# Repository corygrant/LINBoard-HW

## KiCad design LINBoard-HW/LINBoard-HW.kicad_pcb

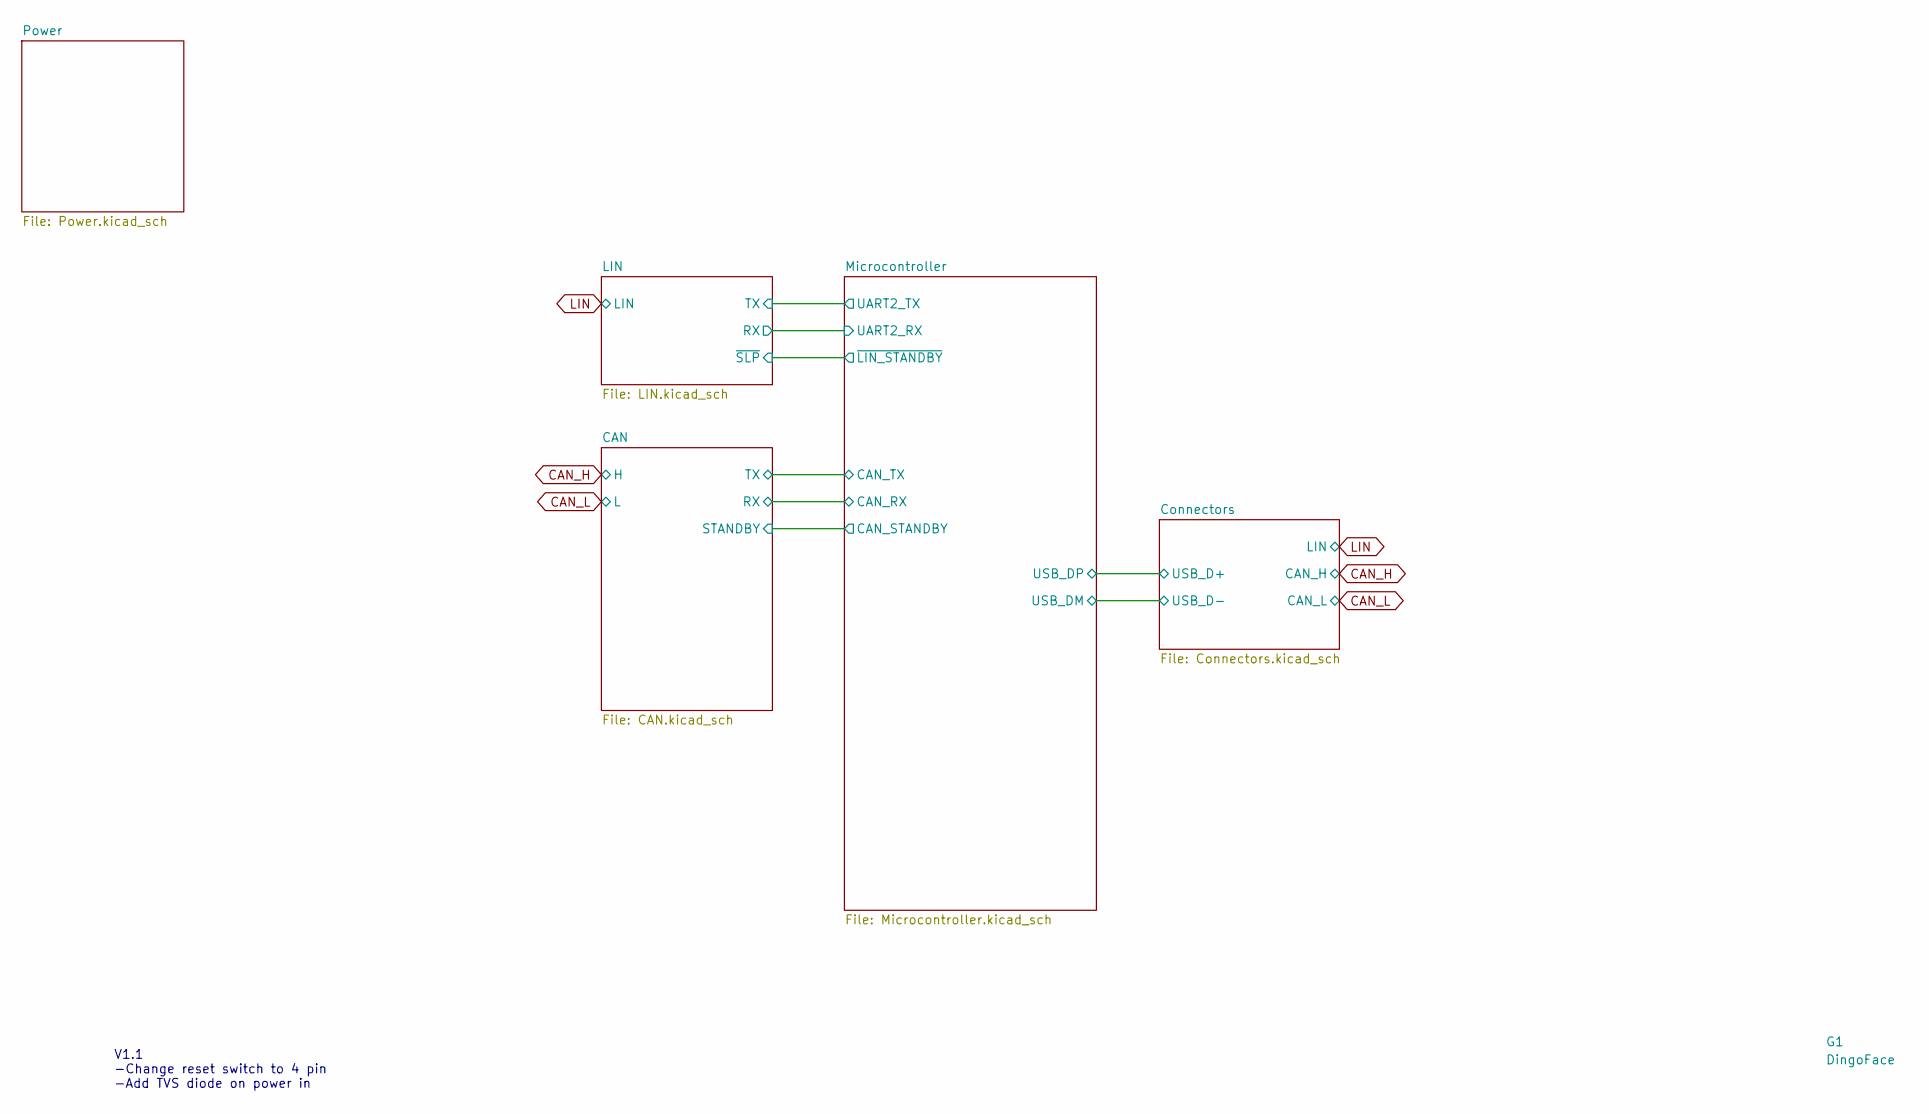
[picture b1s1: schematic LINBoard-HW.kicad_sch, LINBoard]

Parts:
G1: DingoFace; DingoFaceNoFill

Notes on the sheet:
V1.1 -Change reset switch to 4 pin -Add TVS diode on power in

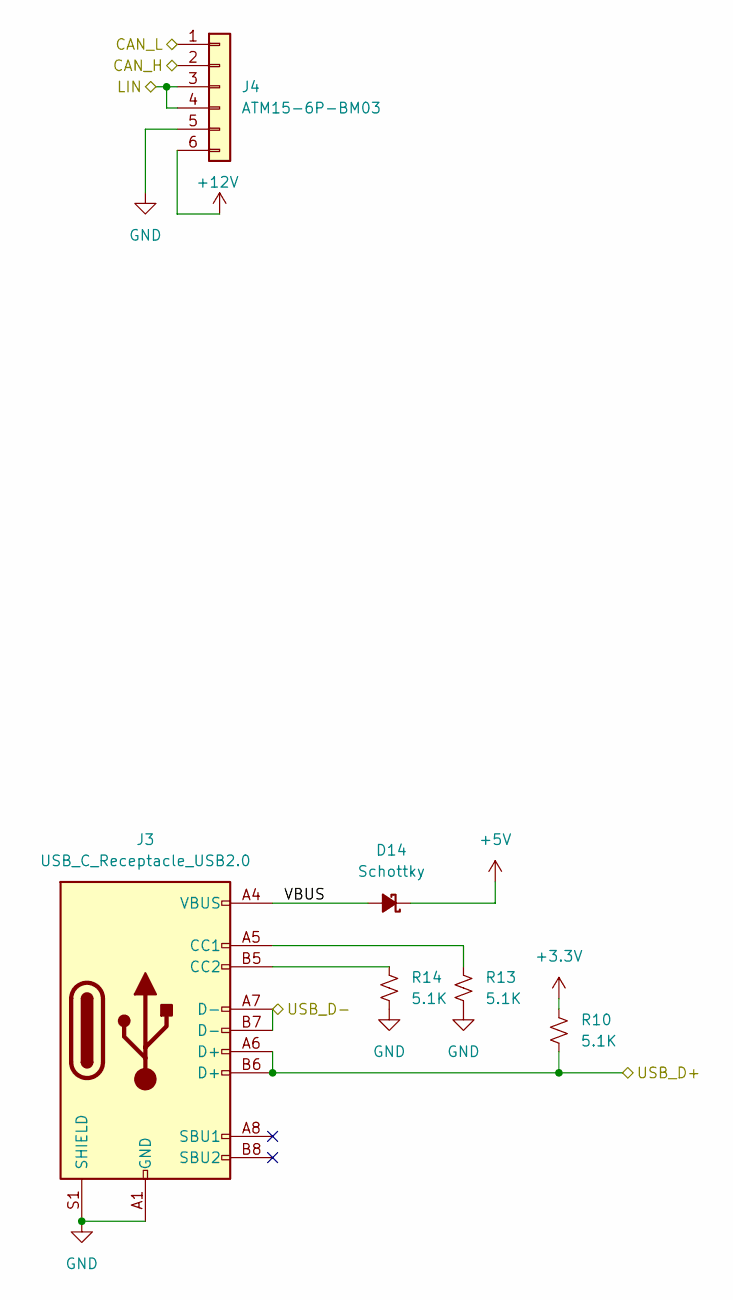
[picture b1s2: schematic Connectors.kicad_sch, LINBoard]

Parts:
D14: Schottky; D_SOD-123; LCSC Part C179426
J3: USB_C_Receptacle_USB2.0; USB_C_Receptacle_GCT_USB4085; Digi-Key_PN 2073-USB4085-GF-ACT-ND
J4: ATM15-6P-BM03; ATM13-6P
R10, R13, R14: 5.1K; R_0805_2012Metric; LCSC Part C27834

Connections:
+3.3V: R10.1; also elsewhere on the board
+5V: D14.1 (K); also elsewhere on the board
+12V: J4.6; also elsewhere on the board
/Connectors/USB_D+: J3.A6 (D+), J3.B6 (D+), R10.2; also elsewhere on the board
/Connectors/USB_D-: J3.A7 (D-), J3.B7 (D-); also elsewhere on the board
/Connectors/VBUS: D14.2 (A), J3.A4 (VBUS), J3.A9 (VBUS), J3.B4 (VBUS), J3.B9 (VBUS)
CAN_H: J4.2; also elsewhere on the board
CAN_L: J4.1; also elsewhere on the board
GND: J3.A1 (GND), J3.A12 (GND), J3.B1 (GND), J3.B12 (GND), J3.S1 (SHIELD), J4.5, R13.2, R14.2; also elsewhere on the board
LIN: J4.3, J4.4; also elsewhere on the board
unnamed: J3.A5 (CC1), R13.1
unnamed: J3.B5 (CC2), R14.1

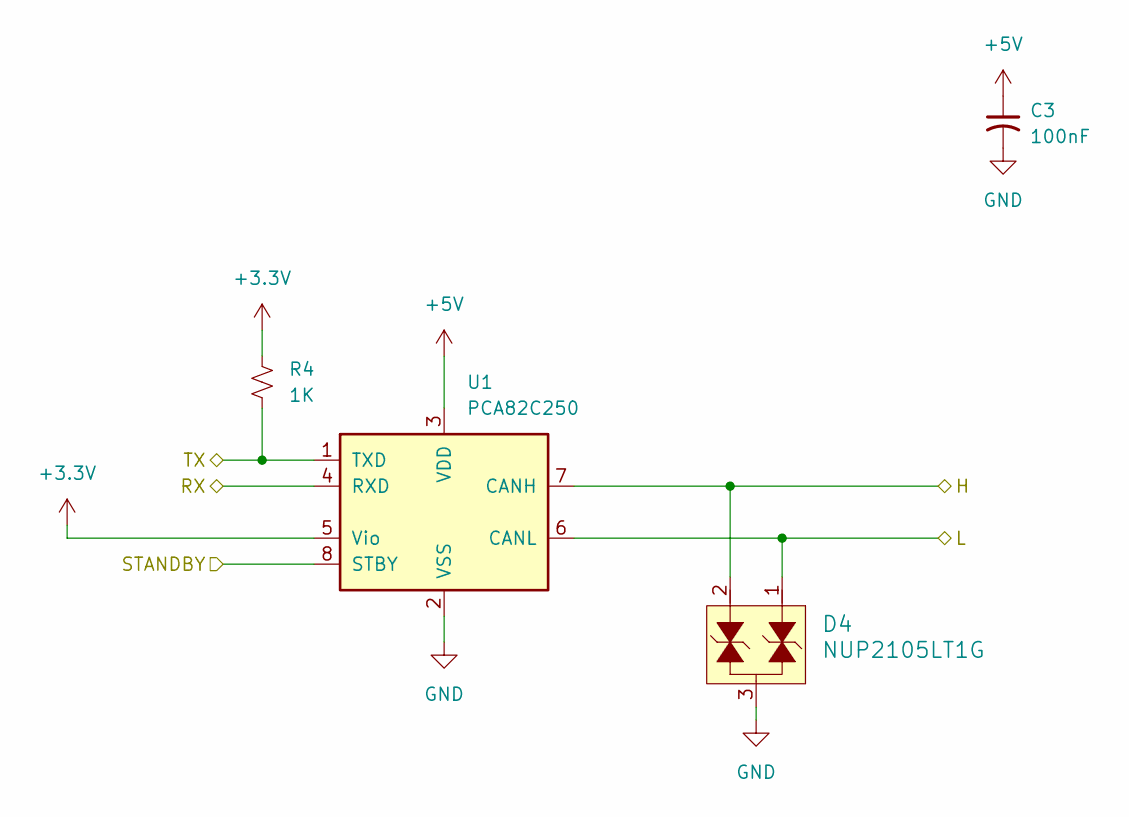
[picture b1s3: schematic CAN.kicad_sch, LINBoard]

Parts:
C3: 100nF; C_0805_2012Metric; LCSC Part C49678
D4: NUP2105LT1G; SOT-23-3; MPN NUP2105LT1G; Digi-Key_PN NUP2105LT1GOSCT-ND
R4: 1K; R_0805_2012Metric; LCSC Part C17513
U1: PCA82C250; SOIC-8_3.9x4.9mm_P1.27mm; LCSC Part C7439

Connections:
+3.3V: R4.1, U1.5 (Vio); also elsewhere on the board
+5V: C3.1, U1.3 (VDD); also elsewhere on the board
/CAN/RX: U1.4 (RXD); also elsewhere on the board
/CAN/STANDBY: U1.8 (STBY); also elsewhere on the board
/CAN/TX: R4.2, U1.1 (TXD); also elsewhere on the board
CAN_H: D4.2, U1.7 (CANH); also elsewhere on the board
CAN_L: D4.1, U1.6 (CANL); also elsewhere on the board
GND: C3.2, D4.3, U1.2 (VSS); also elsewhere on the board

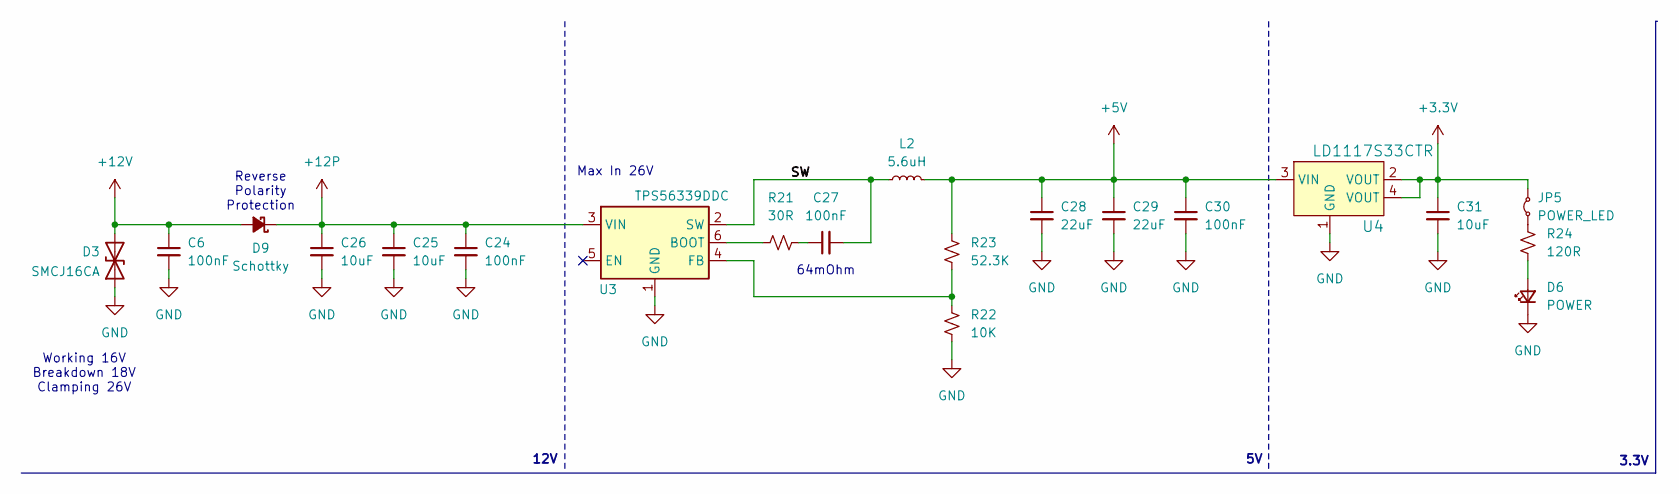
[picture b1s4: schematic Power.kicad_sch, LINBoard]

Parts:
C6: 100nF; C_0805_2012Metric; LCSC Part C15850
C24, C27, C30: 100nF; C_0805_2012Metric; LCSC Part C49678
C25, C26, C31: 10uF; C_0805_2012Metric; LCSC Part C15850
C28, C29: 22uF; C_0805_2012Metric; LCSC Part C45783
D3: SMCJ16CA; DO-214AB_TVS
D6: POWER; LED_0805_2012Metric; LCSC Part C2297
D9: Schottky; D_SOD-123; LCSC Part C179426
JP5: POWER_LED; SolderJumper-2_P1.3mm_Bridged_RoundedPad1.0x1.5mm
L2: 5.6uH; Wuerth_LHMI; LCSC Part C467062
R21: 30R; R_0805_2012Metric; LCSC Part C325808
R22: 10K; R_0805_2012Metric; LCSC Part C17414
R23: 52.3K; R_0805_2012Metric; LCSC Part C17740
R24: 120R; R_0805_2012Metric; LCSC Part C17437
U3: TPS56339DDC; SOT-23-6; LCSC Part C2071106
U4: LD1117S33CTR; SOT-223; MPN LD1117S33CTR; Digi-Key_PN 497-1241-1-ND

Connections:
+3.3V: C31.1, JP5.2 (B), U4.2 (VOUT), U4.4 (VOUT); also elsewhere on the board
+5V: C28.1, C29.1, C30.1, L2.2, R23.2, U4.3 (VIN); also elsewhere on the board
+12P: C24.1, C25.1, C26.1, D9.1 (K), U3.3 (VIN); also elsewhere on the board
+12V: C6.1, D3.2 (A2), D9.2 (A); also elsewhere on the board
/Power/SW: C27.2, L2.1, U3.2 (SW)
GND: C6.2, C24.2, C25.2, C26.2, C28.2, C29.2, C30.2, C31.2, D3.1 (A1), D6.1 (K), R22.1, U3.1 (GND), U4.1 (GND); also elsewhere on the board
unnamed: C27.1, R21.2
unnamed: D6.2 (A), R24.2
unnamed: JP5.1 (A), R24.1
unnamed: R21.1, U3.6 (BOOT)
unnamed: R22.2, R23.1, U3.4 (FB)

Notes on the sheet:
Working 16V Breakdown 18V Clamping 26V
64mOhm
Reverse Polarity Protection
12V
3.3V
Max In 26V

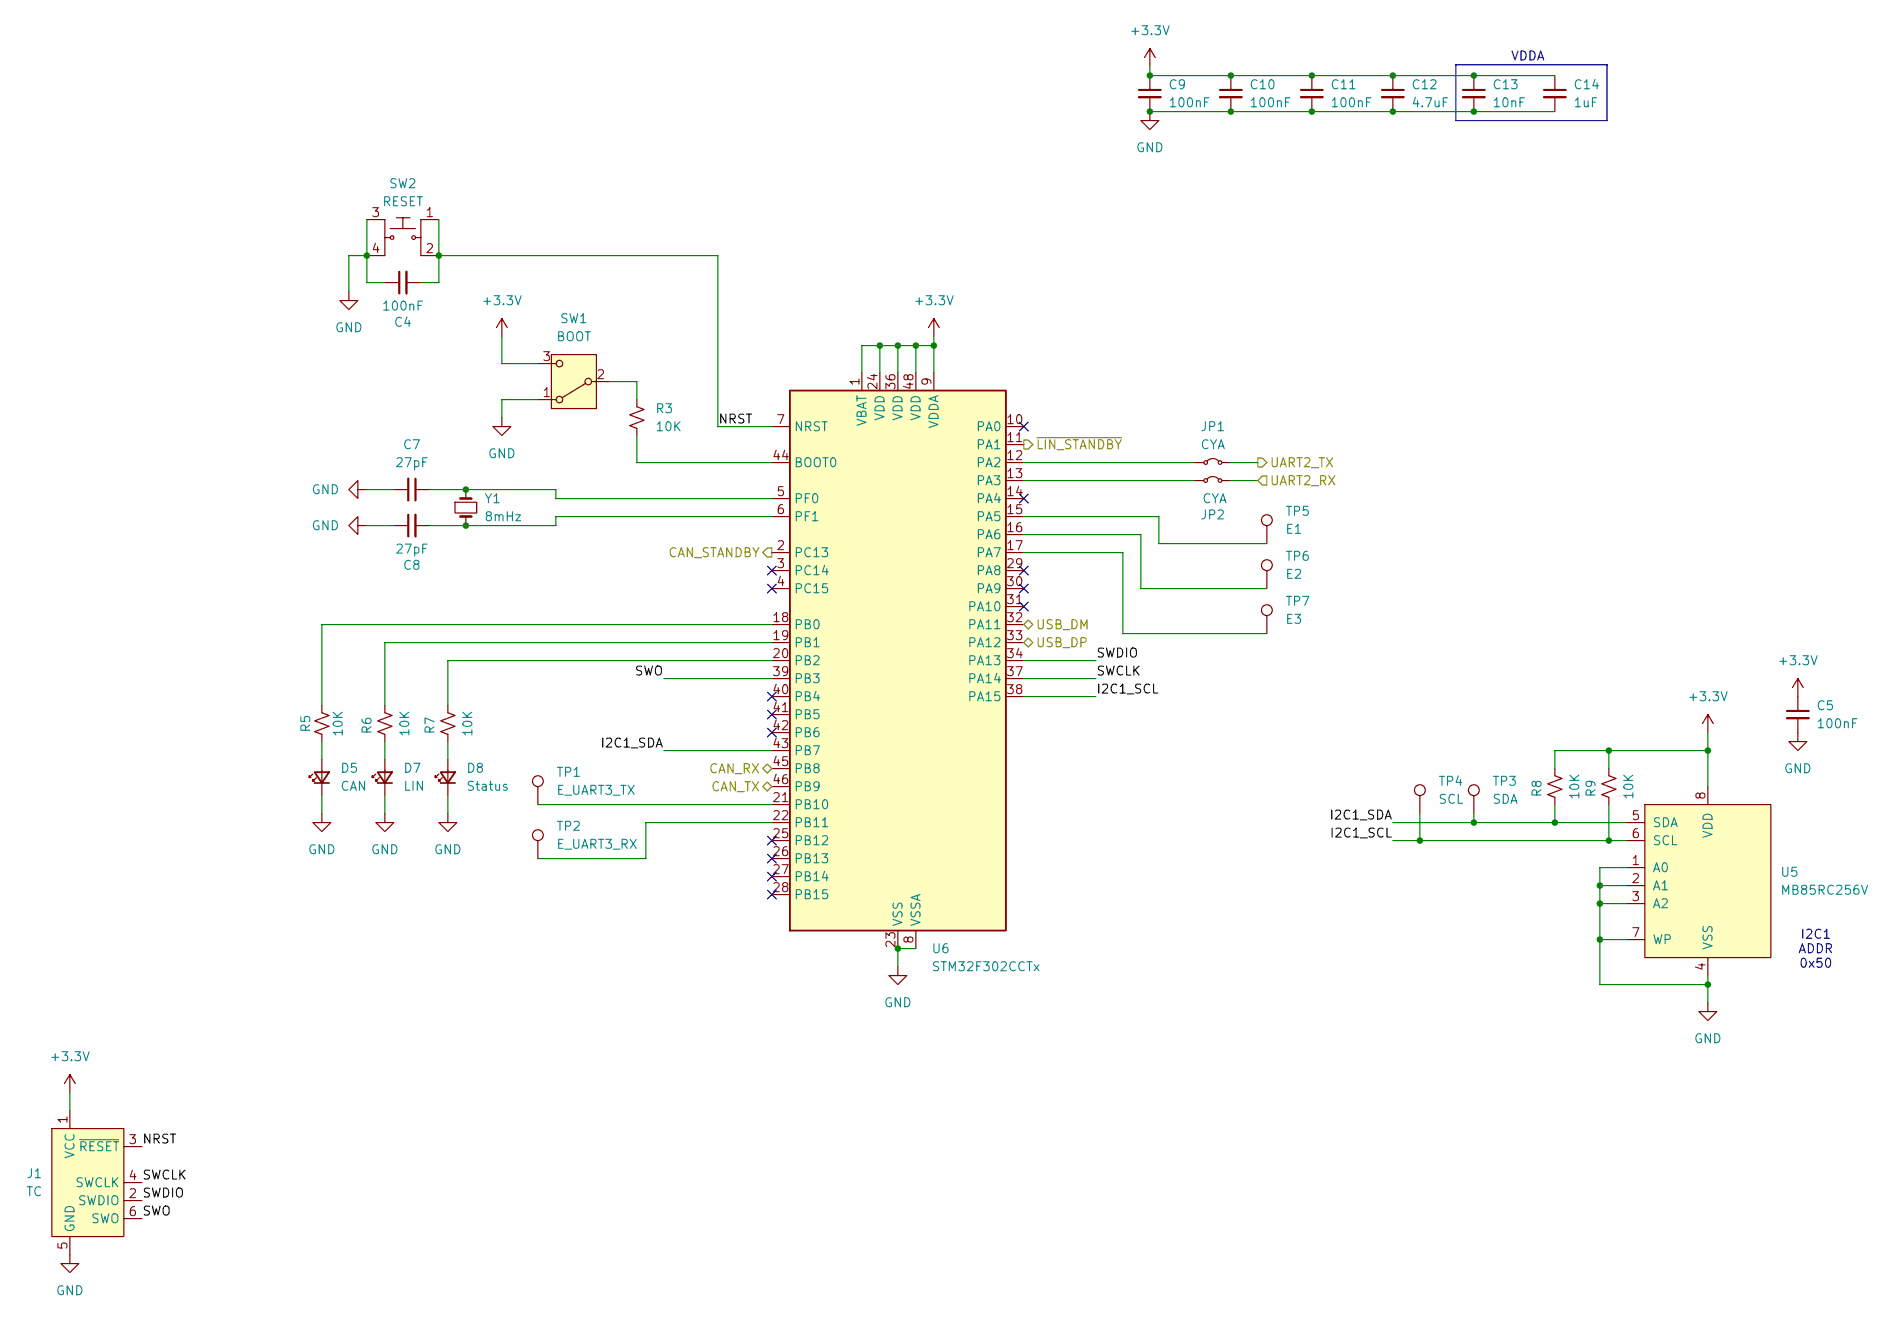
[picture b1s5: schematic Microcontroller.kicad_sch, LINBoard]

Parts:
C4, C5, C9, C10, C11: 100nF; C_0805_2012Metric; LCSC Part C49678
C7, C8: 27pF; C_0805_2012Metric; LCSC Part C1808
C12: 4.7uF; C_0805_2012Metric; LCSC Part C1779
C13: 10nF; C_0805_2012Metric; LCSC Part C1710
C14: 1uF; C_0805_2012Metric; LCSC Part C28323
D5: CAN; LED_0805_2012Metric; LCSC Part C2296
D7: LIN; LED_0805_2012Metric; LCSC Part C2296
D8: Status; LED_0805_2012Metric; LCSC Part C2297
J1: TC; Tag-Connect_TC2030-IDC-NL_2x03_P1.27mm_Vertical
JP1, JP2: CYA; SolderJumper-2_P1.3mm_Bridged2Bar_RoundedPad1.0x1.5mm
R3, R5, R6, R7, R8, R9: 10K; R_0805_2012Metric; LCSC Part C17414
SW1: BOOT; CJS-1200TB
SW2: RESET; SW-SMD_4P-L5.1-W5.1-P3.70-LS6.5-TL_H1.5; LCSC Part C318884
TP1: E_UART3_TX; TestPoint_Keystone_5000-5004_Miniature
TP2: E_UART3_RX; TestPoint_Keystone_5000-5004_Miniature
TP3: SDA; TestPoint_Keystone_5000-5004_Miniature
TP4: SCL; TestPoint_Keystone_5000-5004_Miniature
TP5: E1; TestPoint_Keystone_5000-5004_Miniature
TP6: E2; TestPoint_Keystone_5000-5004_Miniature
TP7: E3; TestPoint_Keystone_5000-5004_Miniature
U5: MB85RC256V; SOIC-8_3.9x4.9mm_P1.27mm; LCSC Part C47538
U6: STM32F302CCTx; LQFP-48_7x7mm_P0.5mm; LCSC Part C262946
Y1: 8mHz; Crystal_SMD_5032-2Pin_5.0x3.2mm_HandSoldering; LCSC Part C144380

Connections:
+3.3V: C5.1, C9.1, C10.1, C11.1, C12.1, C13.1, C14.1, J1.1 (VCC), R8.1, R9.1, SW1.3 (C), U5.8 (VDD), U6.1 (VBAT), U6.9 (VDDA), U6.24 (VDD), U6.36 (VDD), U6.48 (VDD); also elsewhere on the board
/CAN/RX: U6.45 (PB8); also elsewhere on the board
/CAN/STANDBY: U6.2 (PC13); also elsewhere on the board
/CAN/TX: U6.46 (PB9); also elsewhere on the board
/Connectors/USB_D+: U6.33 (PA12); also elsewhere on the board
/Connectors/USB_D-: U6.32 (PA11); also elsewhere on the board
/LIN/RX: JP2.2 (B); also elsewhere on the board
/LIN/TX: JP1.2 (B); also elsewhere on the board
/LIN/~SLP: U6.11 (PA1); also elsewhere on the board
/Microcontroller/I2C1_SCL: R9.2, TP4.1, U5.6 (SCL), U6.38 (PA15)
/Microcontroller/I2C1_SDA: R8.2, TP3.1, U5.5 (SDA), U6.43 (PB7)
/Microcontroller/NRST: C4.2, J1.3 (~RESET), SW2.1, SW2.2, U6.7 (NRST)
/Microcontroller/SWCLK: J1.4 (SWCLK), U6.37 (PA14)
/Microcontroller/SWDIO: J1.2 (SWDIO), U6.34 (PA13)
/Microcontroller/SWO: J1.6 (SWO), U6.39 (PB3)
GND: C4.1, C5.2, C7.2, C8.1, C9.2, C10.2, C11.2, C12.2, C13.2, C14.2, D5.1 (K), D7.1 (K), D8.1 (K), J1.5 (GND), SW1.1 (A), SW2.3, SW2.4, U5.1 (A0), U5.2 (A1), U5.3 (A2), U5.4 (VSS), U5.7 (WP), U6.8 (VSSA), U6.23 (VSS), U6.35 (VSS), U6.47 (VSS); also elsewhere on the board
unnamed: D5.2 (A), R5.2
unnamed: D7.2 (A), R6.2
unnamed: D8.2 (A), R7.2
unnamed: JP1.1 (A), U6.12 (PA2)
unnamed: JP2.1 (A), U6.13 (PA3)
unnamed: R3.2, SW1.2 (B)
unnamed: R3.1, U6.44 (BOOT0)
unnamed: TP5.1, U6.15 (PA5)
unnamed: TP6.1, U6.16 (PA6)
unnamed: TP7.1, U6.17 (PA7)
unnamed: R5.1, U6.18 (PB0)
unnamed: R6.1, U6.19 (PB1)
unnamed: R7.1, U6.20 (PB2)
unnamed: TP1.1, U6.21 (PB10)
unnamed: TP2.1, U6.22 (PB11)
unnamed: C7.1, U6.5 (PF0), Y1.1
unnamed: C8.2, U6.6 (PF1), Y1.2

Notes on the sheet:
VDDA
I2C1 ADDR 0x50

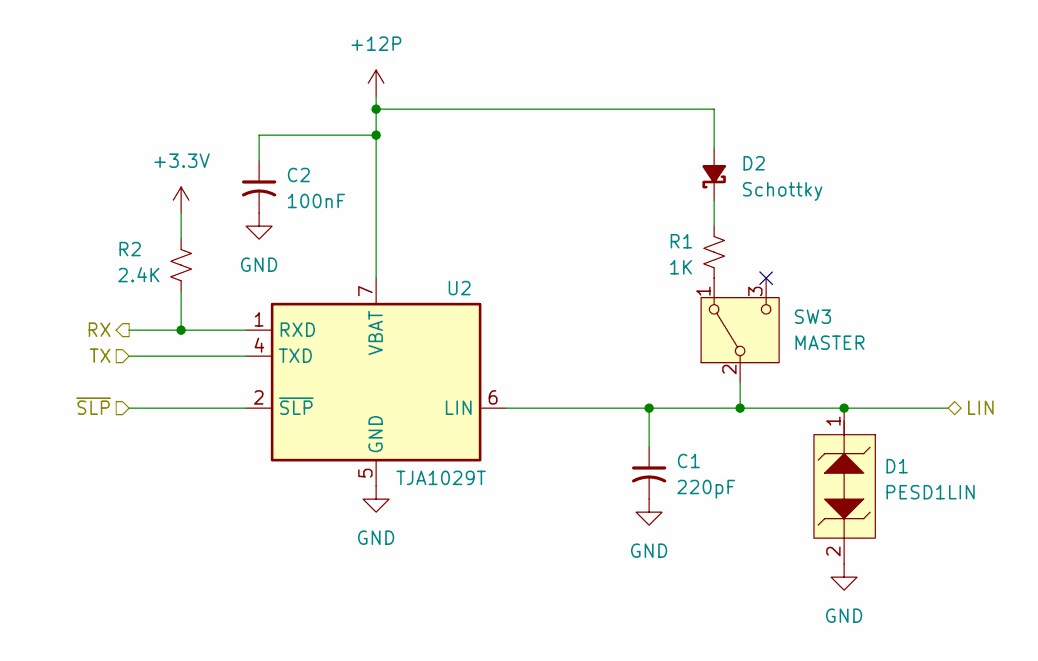
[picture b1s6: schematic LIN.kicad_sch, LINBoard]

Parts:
C1: 220pF; C_0805_2012Metric; LCSC Part C576920
C2: 100nF; C_0805_2012Metric; LCSC Part C49678
D1: PESD1LIN; D_SOD-323; LCSC Part C2858716
D2: Schottky; D_SOD-123; LCSC Part C179426
R1: 1K; R_0805_2012Metric; LCSC Part C17513
R2: 2.4K; R_0805_2012Metric; LCSC Part C17526
SW3: MASTER; CJS-1200TB
U2: TJA1029T; SOIC-8_3.9x4.9mm_P1.27mm; LCSC Part C194435

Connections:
+3.3V: R2.1; also elsewhere on the board
+12P: C2.1, D2.2 (A), U2.7 (VBAT); also elsewhere on the board
/LIN/RX: R2.2, U2.1 (RXD); also elsewhere on the board
/LIN/TX: U2.4 (TXD); also elsewhere on the board
/LIN/~SLP: U2.2 (~SLP); also elsewhere on the board
GND: C1.2, C2.2, D1.2, U2.5 (GND); also elsewhere on the board
LIN: C1.1, D1.1, SW3.2 (B), U2.6 (LIN); also elsewhere on the board
unnamed: D2.1 (K), R1.1
unnamed: R1.2, SW3.1 (A)

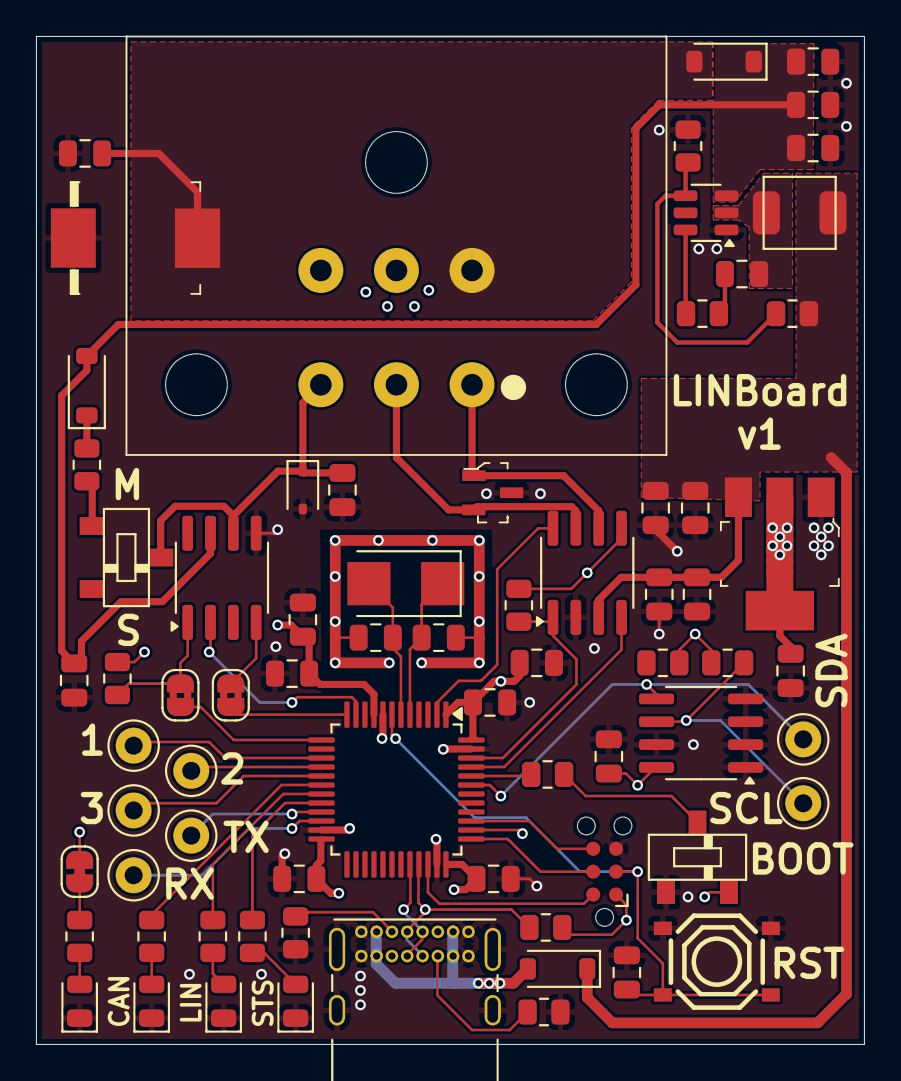
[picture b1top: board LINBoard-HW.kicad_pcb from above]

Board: 4 copper layers, 46.0 x 56.0 mm, 73 parts (1 on the bottom side), 50 nets.

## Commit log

2025-07-17 schematic almost done
2025-08-01 board layout started
2025-08-02 moving some things around
2025-08-15 change usb
2025-08-15 back to ra connectors
2025-08-16 doing some layout
2025-08-17 routing first pass complete
2025-08-18 clean up
2025-08-19 fixed some trace widths
2025-08-23 add fab outputs
2025-08-24 change pinout, export
2025-08-28 add schem pdfs
2025-08-29 add tvs, fix reset button
2025-08-29 add button trace
